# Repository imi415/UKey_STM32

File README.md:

# UKey-STM32

A small stm32 board compatible with Gnuk.

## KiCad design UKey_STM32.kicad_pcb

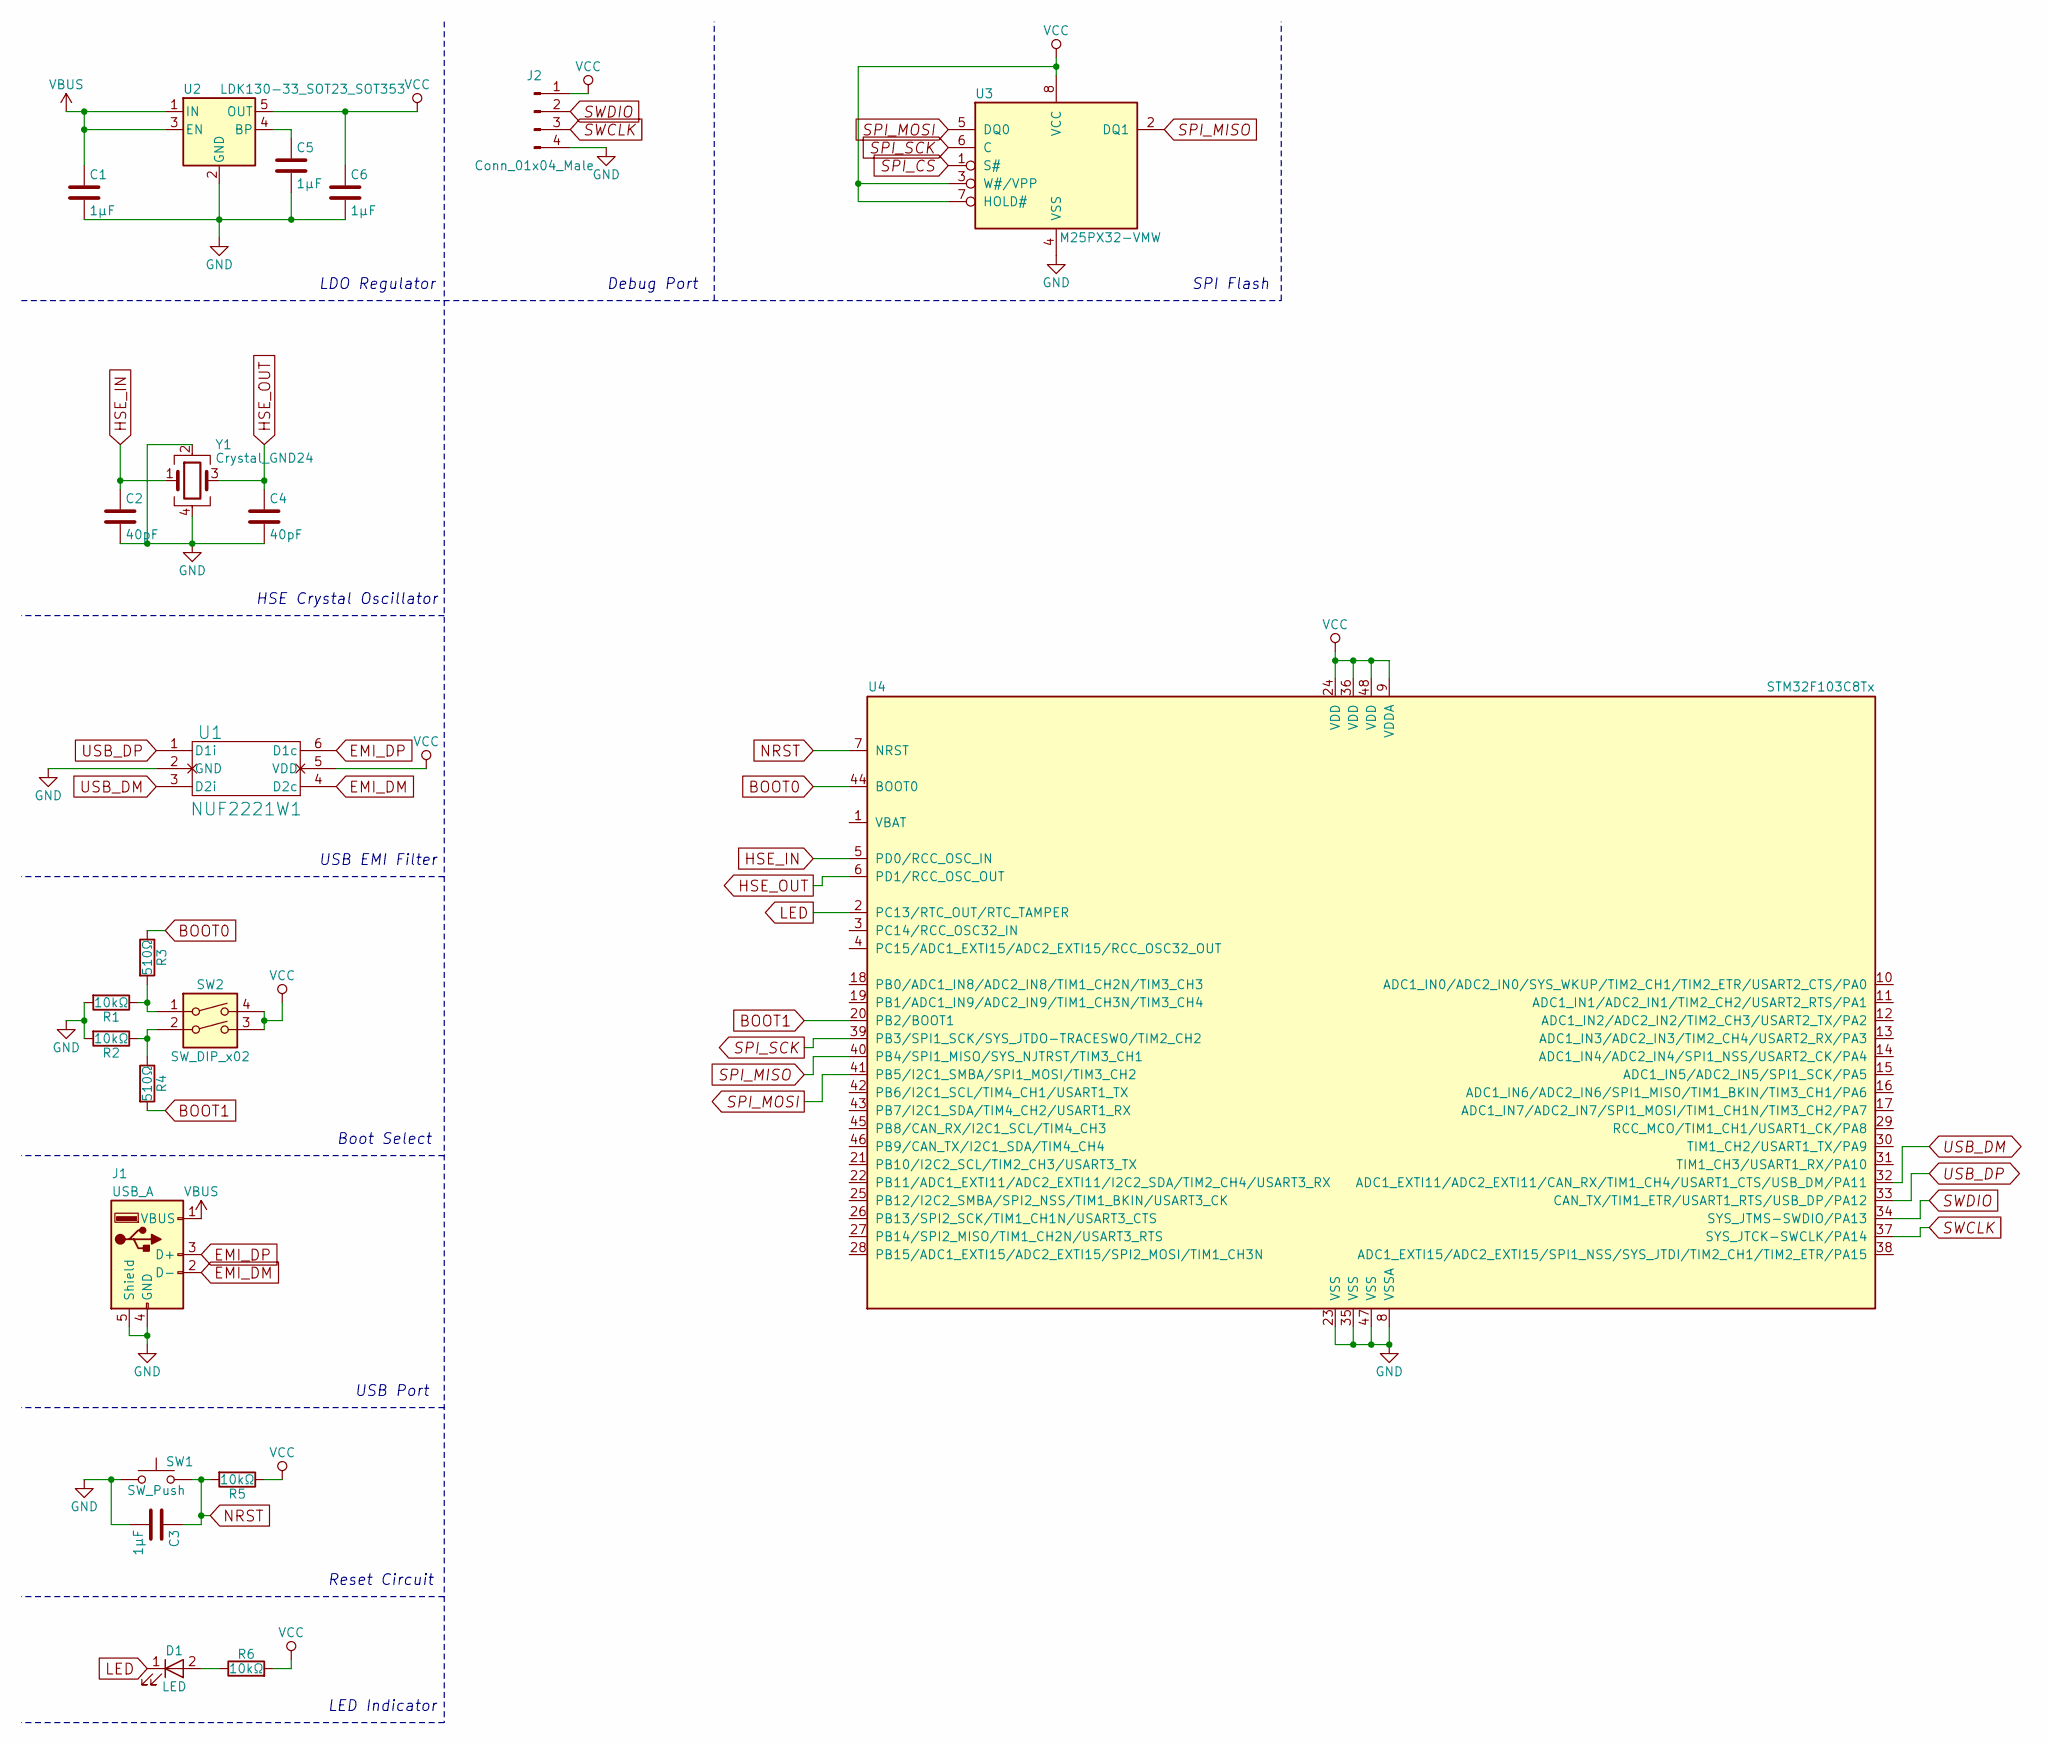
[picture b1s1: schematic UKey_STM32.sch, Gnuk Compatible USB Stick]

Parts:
C1, C3, C5, C6: 1µF; C_0603_HandSoldering
C2, C4: 40pF; C_0603_HandSoldering
D1: LED; LED_0603_HandSoldering
J1: USB_A
J2: Conn_01x04_Male; Pin_Header_Straight_1x04_Pitch2.54mm
R1, R2, R5, R6: 10kΩ; R_0603_HandSoldering
R3, R4: 510Ω; R_0603_HandSoldering
SW1: SW_Push; SW_SPST_FSMSM
SW2: SW_DIP_x02; SW_DIP_x2_W7.62mm_Slide_Copal_CHS-B
U1: NUF2221W1; SOT-363_SC-70-6_Handsoldering
U2: LDK130-33_SOT23_SOT353; SOT-23-5_HandSoldering
U3: M25PX32-VMW; SOIJ-8_5.3x5.3mm_Pitch1.27mm
U4: STM32F103C8Tx; LQFP-48_7x7mm_Pitch0.5mm
Y1: Crystal_GND24; Oscillator_SMD_EuroQuartz_XO32-4pin_3.2x2.5mm_HandSoldering

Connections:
BOOT0: R3.1, U4.44 (BOOT0)
BOOT1: R4.2, U4.20 (PB2/BOOT1)
EMI_DM: J1.2 (D-), U1.4 (D2c)
EMI_DP: J1.3 (D+), U1.6 (D1c)
GND: C1.2, C2.2, C3.2, C4.2, C5.2, C6.2, J1.4 (GND), J1.5 (Shield), J2.4, R1.2, R2.2, SW1.1, U1.2 (GND), U2.2 (GND), U3.4 (VSS), U4.8 (VSSA), U4.23 (VSS), U4.35 (VSS), U4.47 (VSS), Y1.2, Y1.4
HSE_IN: C2.1, U4.5 (PD0/RCC_OSC_IN), Y1.1
HSE_OUT: C4.1, U4.6 (PD1/RCC_OSC_OUT), Y1.3
LED: D1.1 (K), U4.2 (PC13/RTC_OUT/RTC_TAMPER)
NRST: C3.1, R5.2, SW1.2, U4.7 (NRST)
unnamed: C5.1, U2.4 (BP)
unnamed: D1.2 (A), R6.1
unnamed: R1.1, R3.2, SW2.1
unnamed: R2.1, R4.1, SW2.2
SPI_CS: U3.1 (S#)
SPI_MISO: U3.2 (DQ1), U4.40 (PB4/SPI1_MISO/SYS_NJTRST/TIM3_CH1)
SPI_MOSI: U3.5 (DQ0), U4.41 (PB5/I2C1_SMBA/SPI1_MOSI/TIM3_CH2)
SPI_SCK: U3.6 (C), U4.39 (PB3/SPI1_SCK/SYS_JTDO-TRACESWO/TIM2_CH2)
SWCLK: J2.3, U4.37 (SYS_JTCK-SWCLK/PA14)
SWDIO: J2.2, U4.34 (SYS_JTMS-SWDIO/PA13)
USB_DM: U1.3 (D2i), U4.32 (ADC1_EXTI11/ADC2_EXTI11/CAN_RX/TIM1_CH4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)
USB_DP: U1.1 (D1i), U4.33 (CAN_TX/TIM1_ETR/USART1_RTS/USB_DP/PA12)
VBUS: C1.1, J1.1 (VBUS), U2.1 (IN), U2.3 (EN)
VCC: C6.1, J2.1, R5.1, R6.2, SW2.3, SW2.4, U1.5 (VDD), U2.5 (OUT), U3.3 (W#/VPP), U3.7 (HOLD#), U3.8 (VCC), U4.9 (VDDA), U4.24 (VDD), U4.36 (VDD), U4.48 (VDD)

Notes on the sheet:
LED Indicator
Reset Circuit
Boot Select
LDO Regulator
HSE Crystal Oscillator
USB EMI Filter
USB Port
Debug Port
SPI Flash

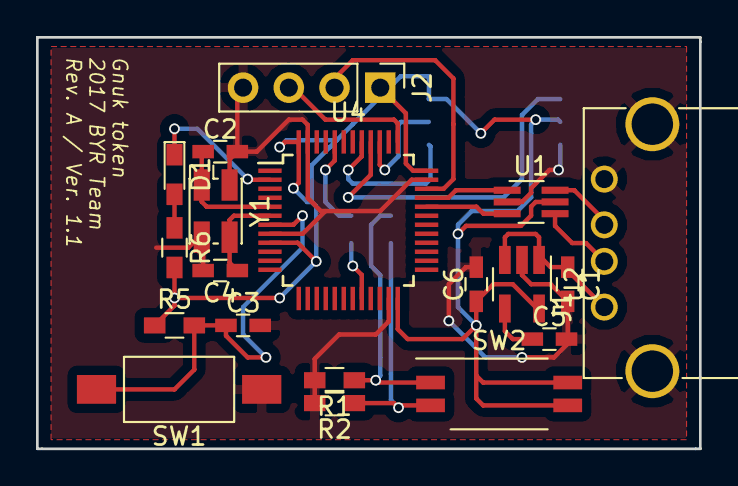
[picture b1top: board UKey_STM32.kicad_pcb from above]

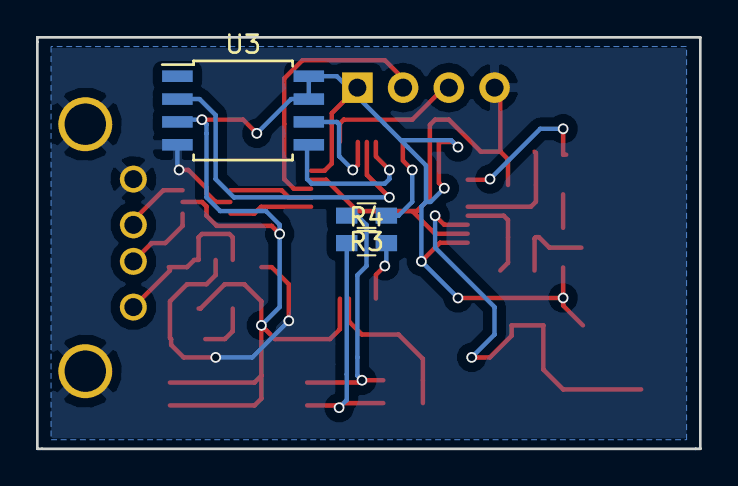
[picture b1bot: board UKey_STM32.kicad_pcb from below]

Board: 2 copper layers, 36.8 x 22.9 mm, 22 parts (3 on the bottom side), 22 nets.

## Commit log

2017-10-11 Initial commit, Rev.A
2017-10-11 Added README.md
2017-10-11 Fixed LDO EN Pin.
2017-12-15 Updated board.
